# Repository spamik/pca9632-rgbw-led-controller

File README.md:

# PCA9632 RGBW LED controller

This project is a PCB design files for RGBW LED controller based on PCA9632 chip. This controller was designed for controlling RGBS LED strips on 3D printer. PCA9632 chip has support in Marlin firmware so with this PCB it's needed only connect LED strips, power supply and I2C to printer controller.

##### Main highlights:
  * Molex Micro-Fit connectors for all outside connections (power supply, I2C communication and two 5 pin outputs for LED strips)
  * 24V compatible
  * Included MOSFETs

##### Project contents:
  * **pca9632_lec_controller_pcb:** KICAD source files for PCB and schematics
  * **gerber:** gerber factory files for PCB (compatible with JLCPCB)
  * **box_3d_models:** 3D printable box for electronics

##### Picture of assembled PCB:

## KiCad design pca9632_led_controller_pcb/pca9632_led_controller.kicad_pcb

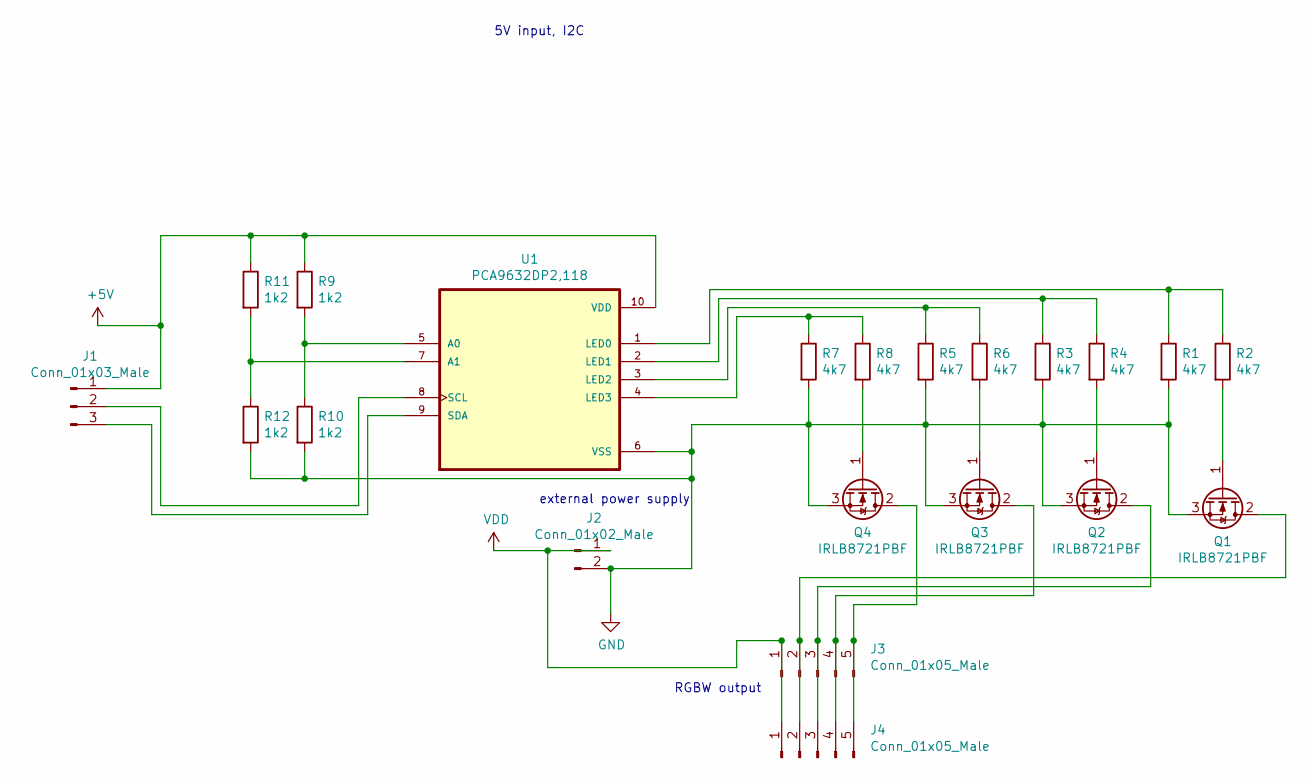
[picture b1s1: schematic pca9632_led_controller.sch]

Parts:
J1: Conn_01x03_Male; Molex_Micro-Fit_3.0_43650-0300_1x03_P3.00mm_Horizontal
J2: Conn_01x02_Male; Molex_Micro-Fit_3.0_43650-0200_1x02_P3.00mm_Horizontal
J3, J4: Conn_01x05_Male; Molex_Micro-Fit_3.0_43650-0500_1x05_P3.00mm_Horizontal
Q1, Q2, Q3, Q4: IRLB8721PBF; TO-220-3_Vertical
R1, R2, R3, R4, R5, R6, R7, R8: 4k7; R_0805_2012Metric_Pad1.20x1.40mm_HandSolder
R9, R10, R11, R12: 1k2; R_0805_2012Metric_Pad1.20x1.40mm_HandSolder
U1: PCA9632DP2,118; SOP50P490X110-10N; PARTREV 5

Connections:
+5V: J1.1, R9.1, R11.1, U1.10 (VDD)
GND: J2.2, Q1.3 (S), Q2.3 (S), Q3.3 (S), Q4.3 (S), R1.2, R3.2, R5.2, R7.2, R10.2, R12.2, U1.6 (VSS)
unnamed: J1.2, U1.8 (SCL)
unnamed: J1.3, U1.9 (SDA)
unnamed: J3.2, J4.2, Q1.2 (D)
unnamed: J3.3, J4.3, Q2.2 (D)
unnamed: J3.4, J4.4, Q3.2 (D)
unnamed: J3.5, J4.5, Q4.2 (D)
unnamed: Q1.1 (G), R2.2
unnamed: Q2.1 (G), R4.2
unnamed: Q3.1 (G), R6.2
unnamed: Q4.1 (G), R8.2
unnamed: R1.1, R2.1, U1.1 (LED0)
unnamed: R3.1, R4.1, U1.2 (LED1)
unnamed: R5.1, R6.1, U1.3 (LED2)
unnamed: R7.1, R8.1, U1.4 (LED3)
unnamed: R9.2, R10.1, U1.5 (A0)
unnamed: R11.2, R12.1, U1.7 (A1)
VDD: J2.1, J3.1, J4.1

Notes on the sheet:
5V input, I2C
external power supply
RGBW output

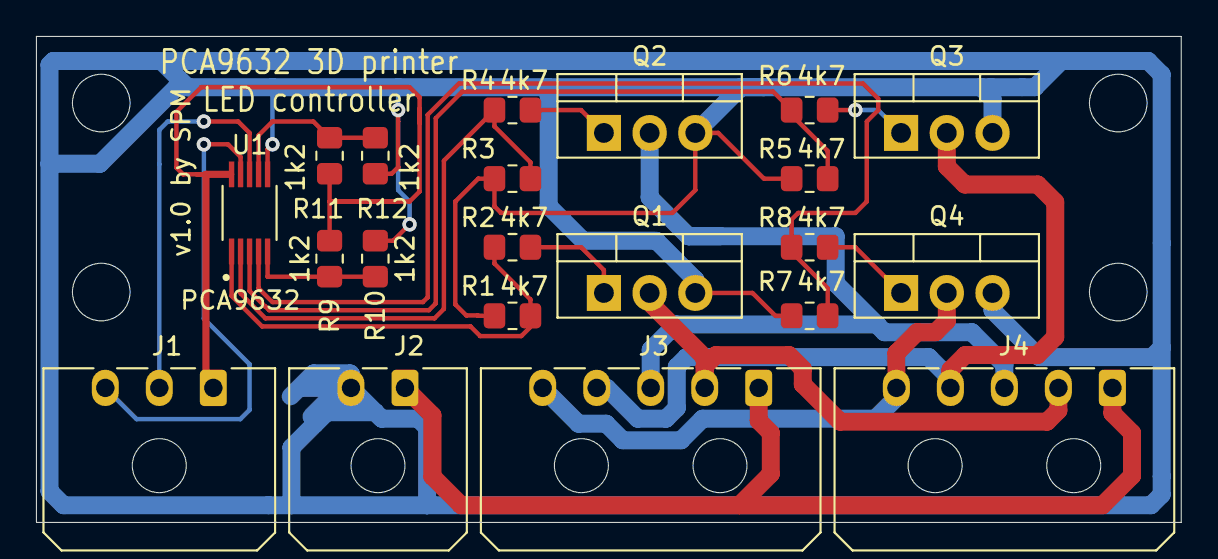
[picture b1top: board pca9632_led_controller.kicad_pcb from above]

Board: 2 copper layers, 63.6 x 27.0 mm, 21 parts (0 on the bottom side), 19 nets.

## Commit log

2022-12-18 Initial import
2022-12-19 Added photo of assembled PCB
2022-12-21 Added README.md file
